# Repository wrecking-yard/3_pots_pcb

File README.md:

# 3 Pots PCB

Crappy "design" of "integration" board for 3 potentiometers.
(I have no idea what I am doing, you probably don't want to use it; PRs welcome though :))

female pin header and screw terminal block added for convenience.

Generic RK097 dual pot is a modification of KiCad library element; excluded from this repo license.

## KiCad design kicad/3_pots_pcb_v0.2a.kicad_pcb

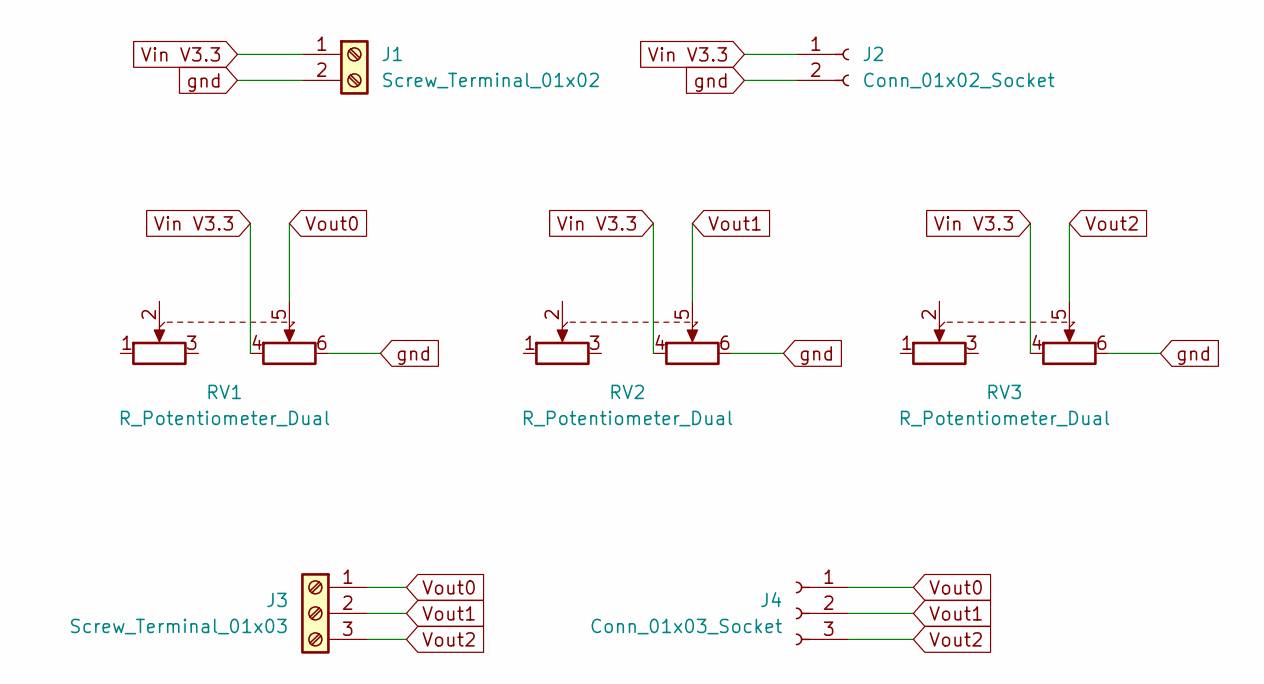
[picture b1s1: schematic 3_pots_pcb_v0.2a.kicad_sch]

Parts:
J1: Screw_Terminal_01x02; TerminalBlock_MetzConnect_Type055_RT01502HDWU_1x02_P5.00mm_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
J2: Conn_01x02_Socket; PinSocket_1x02_P2.54mm_Vertical
J3: Screw_Terminal_01x03; TerminalBlock_MetzConnect_Type055_RT01503HDWU_1x03_P5.00mm_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
J4: Conn_01x03_Socket; PinSocket_1x03_P2.54mm_Vertical
RV1, RV2, RV3: R_Potentiometer_Dual; Potentiometer_Generic_AliExpress_RK097_Dual_Horizontal

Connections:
Vin V3.3: J1.1, J2.1, RV1.4, RV2.4, RV3.4
Vout0: J3.1, J4.1, RV1.5
Vout1: J3.2, J4.2, RV2.5
Vout2: J3.3, J4.3, RV3.5
gnd: J1.2, J2.2, RV1.6, RV2.6, RV3.6

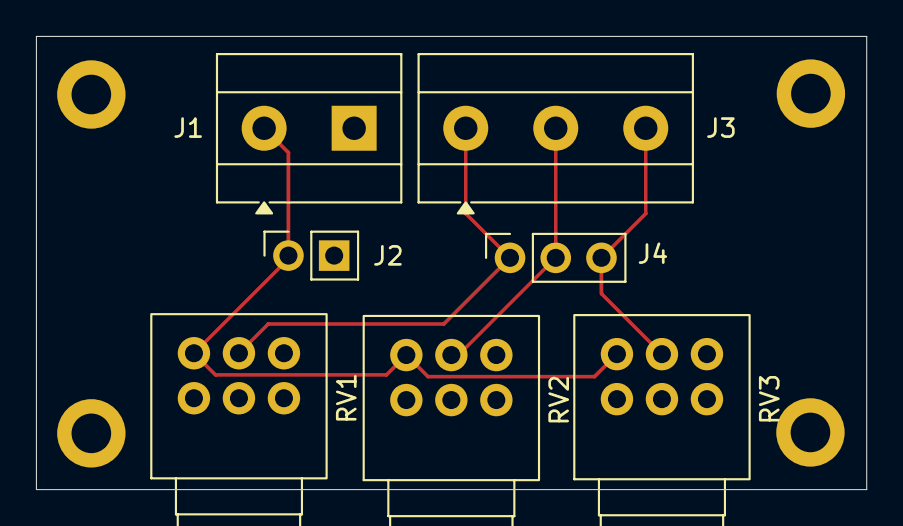
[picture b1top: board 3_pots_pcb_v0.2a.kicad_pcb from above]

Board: 2 copper layers, 46.1 x 25.2 mm, 7 parts (0 on the bottom side), 5 nets.

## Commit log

2025-04-21 README update
2025-05-02 add changelog, update pads, rename gerbers dir
2025-05-03 updated pics
